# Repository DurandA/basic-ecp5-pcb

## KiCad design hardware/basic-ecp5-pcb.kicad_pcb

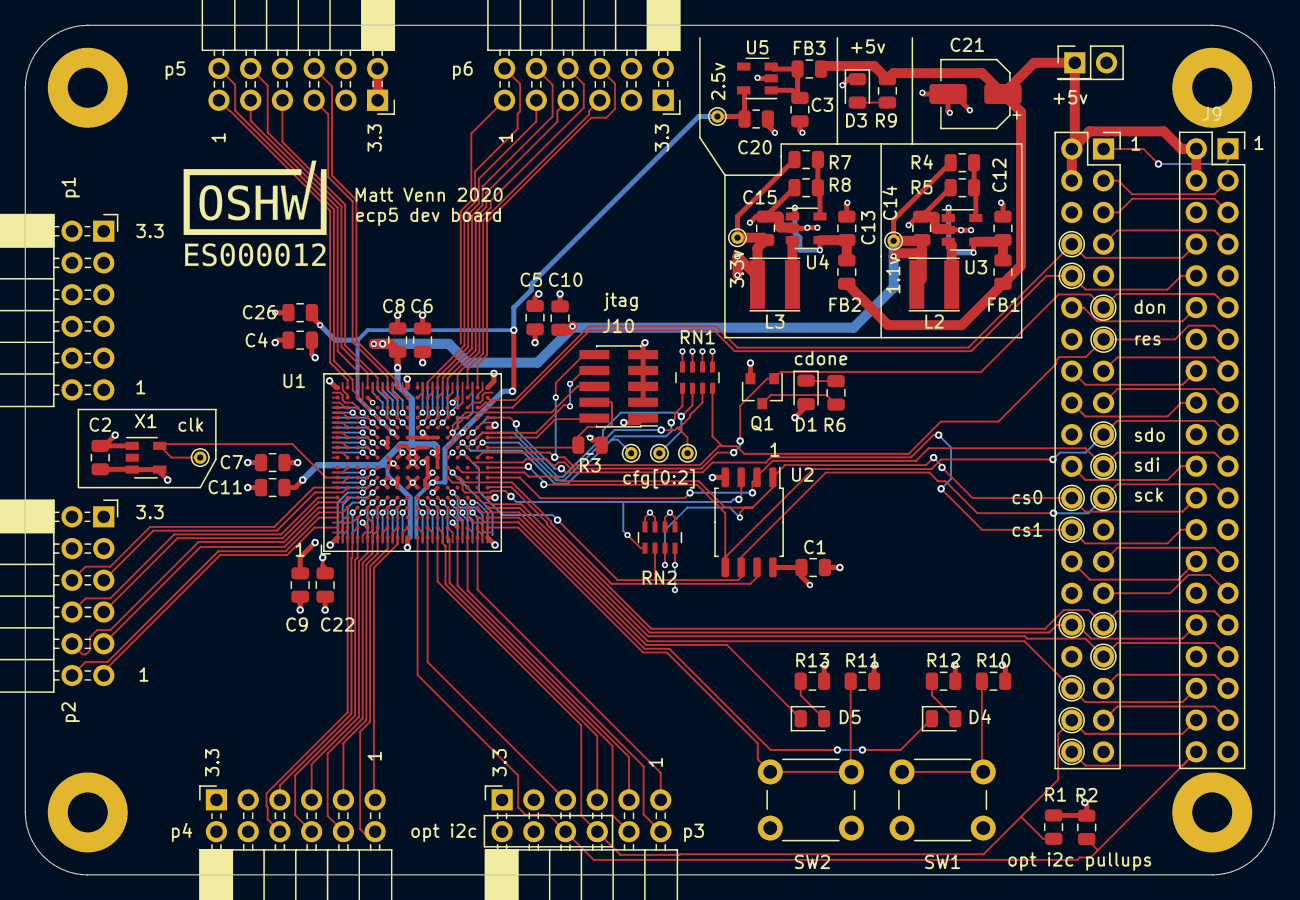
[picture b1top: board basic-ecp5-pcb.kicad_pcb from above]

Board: 4 copper layers, 100.0 x 68.0 mm, 73 parts (0 on the bottom side), 107 nets.

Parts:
C1, C2, C4, C5, C6, C8, C9, C10, C22: 100n; C_0805_2012Metric
C3, C20: 1u; C_0805_2012Metric
C7, C11, C15, C26: 10u; C_0805_2012Metric
C12, C13: 4.7u; C_0805_2012Metric
C14: 22u; C_0805_2012Metric
C21: CP; CP_Elec_5x5.4
D1, D3, D4, D5: LED; LED_0805_2012Metric
FB1, FB2, FB3: Ferrite_Bead_Small; L_0805_2012Metric
H1, H2, H3, H4: MountingHole_Pad; MountingHole_3.2mm_M3_Pad
J1: Conn_01x02; PinHeader_2x01_P2.54mm_Vertical
J2, J9: Conn_02x20_Odd_Even; PinSocket_2x20_P2.54mm_Vertical
J3, J4, J5, J6, J7, J8: Conn_02x06_Odd_Even; PinSocket_2x06_P2.54mm_Horizontal
J10: Conn_02x05_Odd_Even; PinHeader_2x05_P1.27mm_Vertical_SMD
L2, L3: 2.2uH; L_Taiyo-Yuden_NR-40xx
Q1: Q_NMOS_GSD; SOT-23
R1, R2, R3, R10, R11: 10k; R_0805_2012Metric
R4: 100k; R_0805_2012Metric
R5: 120k; R_0805_2012Metric
R6, R9, R12, R13: 200R; R_0805_2012Metric
R7: 68k; R_0805_2012Metric
R8: 15k; R_0805_2012Metric
RN1, RN2: 10k; R_Array_Concave_4x0603
SW1, SW2: SW_Push; SW_PUSH_6mm
TP1: 3.3v; TestPoint_THTPad_D1.0mm_Drill0.5mm
TP2, TP4, TP7: TestPoint; TestPoint_THTPad_D1.0mm_Drill0.5mm
TP3: 2.5v; TestPoint_THTPad_D1.0mm_Drill0.5mm
TP5: clock; TestPoint_THTPad_D1.0mm_Drill0.5mm
TP6: 1.1v; TestPoint_THTPad_D1.0mm_Drill0.5mm
U1: ECP5U_45_CABGA256; BGA-256_14.0x14.0mm_Layout16x16_P0.8mm_Ball0.45mm_Pad0.32mm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
U2: IS25LP016D-JBLE; SOIC-8_5.23x5.23mm_P1.27mm
U3, U4: TLV62568DBV; SOT-23-5
U5: TLV73325PDBV; SOT-23-5
X1: SiT2001B; SOT-23-5

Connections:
+1V1: C8.1, C9.1, C10.1, C11.1, C14.1, L2.2, R4.2, TP6.1, U1.G6, U1.G7, U1.G9, U1.L8, U1.L9, U1.L10
+2V5: C20.1, C22.1, C26.1, TP3.1, U1.E13, U1.F12, U1.G11, U1.L7, U1.N11, U5.5
+3.3VP: C1.1, C2.1, C4.1, C5.1, C6.1, C7.1, C15.1, D1.2, J3.1, J3.2, J4.1, J4.2, J5.1, J5.2, J6.1, J6.2, J7.1, J7.2, J8.1, J8.2, J10.1, L3.2, R1.1, R2.1, R7.2, R10.2, R11.2, R12.2, R13.2, RN1.5, RN1.7, RN2.5, RN2.6, RN2.7, RN2.8, TP1.1, U1.F6, U1.F7, U1.F10, U1.F11, U1.H6, U1.H7, U1.H11, U1.J6, U1.J7, U1.J11, U1.K11, U1.L6, U1.L11, U2.8, X1.3, X1.4
+5V: C21.1, FB1.2, FB2.2, FB3.2, J1.1, J2.2, J2.4, J9.2, J9.4, R9.2
/fpga/cfg_0: RN1.1, TP2.1, U1.N10
/fpga/cfg_1: RN1.2, TP4.1, U1.P10
/fpga/cfg_2: RN1.3, TP7.1, U1.R10
/fpga/tck: J10.4, R3.2, U1.T10
/fpga/tdi: J10.8, U1.R11
/fpga/tdo: J10.6, U1.M10
/fpga/tms: J10.2, U1.T11
/gp0: J2.27, J9.27
/gp1: J2.28, J9.28
/gp2: J2.3, J9.3
/gp3: J2.5, J9.5
/gp4: J2.7, J9.7
/gp5: J2.29, J9.29
/gp18: J2.12, J9.12
/gp19: J2.35, J9.35
/gp22: J2.15, J9.15
/gp23: J2.16, J9.16
/gp24: J2.18, J9.18
/gp25: J2.22, J9.22
/gp26: J2.37, J9.37
/pi_3v3: J2.1, J9.1
/pi_3v3_2: J2.17, J9.17
GND: C1.2, C2.2, C3.2, C4.2, C5.2, C6.2, C7.2, C8.2, C9.2, C10.2, C11.2, C12.2, C13.2, C14.2, C15.2, C20.2, C21.2, C22.2, C26.2, D3.1, H1.1, H2.1, H3.1, H4.1, J1.2, J2.6, J2.9, J2.14, J2.20, J2.25, J2.30, J2.34, J2.39, J3.3, J3.4, J4.3, J4.4, J5.3, J5.4, J6.3, J6.4, J7.3, J7.4, J8.3, J8.4, J9.6, J9.9, J9.14, J9.20, J9.25, J9.30, J9.34, J9.39, J10.3, J10.5, J10.7, J10.9, Q1.2, R3.1, R5.1, R8.1, RN1.6, RN1.8, SW1.2, SW2.2, U1.A1, U1.A16, U1.D2, U1.D15, U1.F8, U1.F9, U1.G8, U1.G10, U1.H1, U1.H8, U1.H9, U1.H10, U1.H16, U1.J8, U1.J9, U1.J10, U1.K6, U1.K7, U1.K8, U1.K9, U1.K10, U1.N2, U1.N15, U1.T1, U1.T5, U1.T12, U1.T16, U2.4, U3.2, U4.2, U5.2, X1.1
unnamed: C3.1, FB3.1, U5.1, U5.3
unnamed: C12.1, FB1.1, U3.1, U3.4
unnamed: C13.1, FB2.1, U4.1, U4.4
unnamed: D1.1, R6.1
unnamed: D3.2, R9.1
unnamed: D4.2, R12.1
unnamed: D5.2, R13.1
unnamed: L2.1, U3.3
unnamed: L3.1, U4.3
unnamed: Q1.3, R6.2
unnamed: R4.1, R5.2, U3.5
unnamed: R7.1, R8.2, U4.5
button1: R10.1, SW1.1, U1.R2
button2: R11.1, SW2.1, U1.T2
cdone: J2.11, J9.11, Q1.1, U1.P9
ce1: J2.26, J9.26, U1.T13
clk: TP5.1, U1.A7, X1.5
creset: J2.13, J9.13, J10.10, RN1.4, U1.R9
gp6: J2.31, J9.31, U1.T6
gp12: J2.32, J9.32, U1.R5
gp13: J2.33, J9.33, U1.T4
gp14: J2.8, J9.8, U1.T15
gp15: J2.10, J9.10, U1.T14
gp16: J2.36, J9.36, U1.R4
led1: D4.1, U1.R3
led2: D5.1, U1.T3
p1_1: J3.11, U1.A8
p1_2: J3.9, U1.A10
p1_3: J3.7, U1.A12
p1_4: J3.5, U1.A14
p1_7: J3.12, U1.A9
p1_8: J3.10, U1.A11
p1_9: J3.8, U1.A13
p1_10: J3.6, U1.A15
p2_1: J4.11, U1.A2
p2_2: J4.9, U1.B4
p2_3: J4.7, U1.B5
p2_4: J4.5, U1.B6
p2_7: J4.12, U1.A3
p2_8: J4.10, U1.A4
p2_9: J4.8, U1.A5
p2_10: J4.6, U1.A6
p3_1: J5.11, U1.R1
p3_2: J5.9, U1.N1
p3_3: J5.7, U1.L2
p3_4: J5.5, U1.K1
p3_7: J5.12, U1.P1
p3_8: J5.10, U1.M1
p3_9: J2.38, J5.8, J9.38, R1.2, U1.L1
p3_10: J2.40, J5.6, J9.40, R2.2, U1.J1
p4_1: J6.11, U1.G1
p4_2: J6.9, U1.E1
p4_3: J6.7, U1.D1
p4_4: J6.5, U1.C2
p4_7: J6.12, U1.F1
p4_8: J6.10, U1.E2
p4_9: J6.8, U1.C1
p4_10: J6.6, U1.B1
p5_1: J7.11, U1.B16
p5_2: J7.9, U1.C16
p5_3: J7.7, U1.E16
p5_4: J7.5, U1.F16
p5_7: J7.12, U1.C15
p5_8: J7.10, U1.D16
p5_9: J7.8, U1.E15
p5_10: J7.6, U1.G16
p6_1: J8.11, U1.J16
p6_2: J8.9, U1.L16
p6_3: J8.7, U1.M16
p6_4: J8.5, U1.P16
p6_7: J8.12, U1.K16
p6_8: J8.10, U1.L15
p6_9: J8.8, U1.N16
p6_10: J8.6, U1.R16
sd_clk: J2.23, J9.23, RN2.2, U1.N9, U2.6
sd_cs: J2.24, J9.24, RN2.3, U1.N8, U2.1
sd_io2: RN2.1, U1.M7, U2.3
sd_io3: RN2.4, U1.N7, U2.7
sdi: J2.21, J9.21, U1.T7, U2.2
sdo: J2.19, J9.19, U1.T8, U2.5

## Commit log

2020-12-06 Fanout BGA center
2020-12-06 Fanout BGA outer #1
